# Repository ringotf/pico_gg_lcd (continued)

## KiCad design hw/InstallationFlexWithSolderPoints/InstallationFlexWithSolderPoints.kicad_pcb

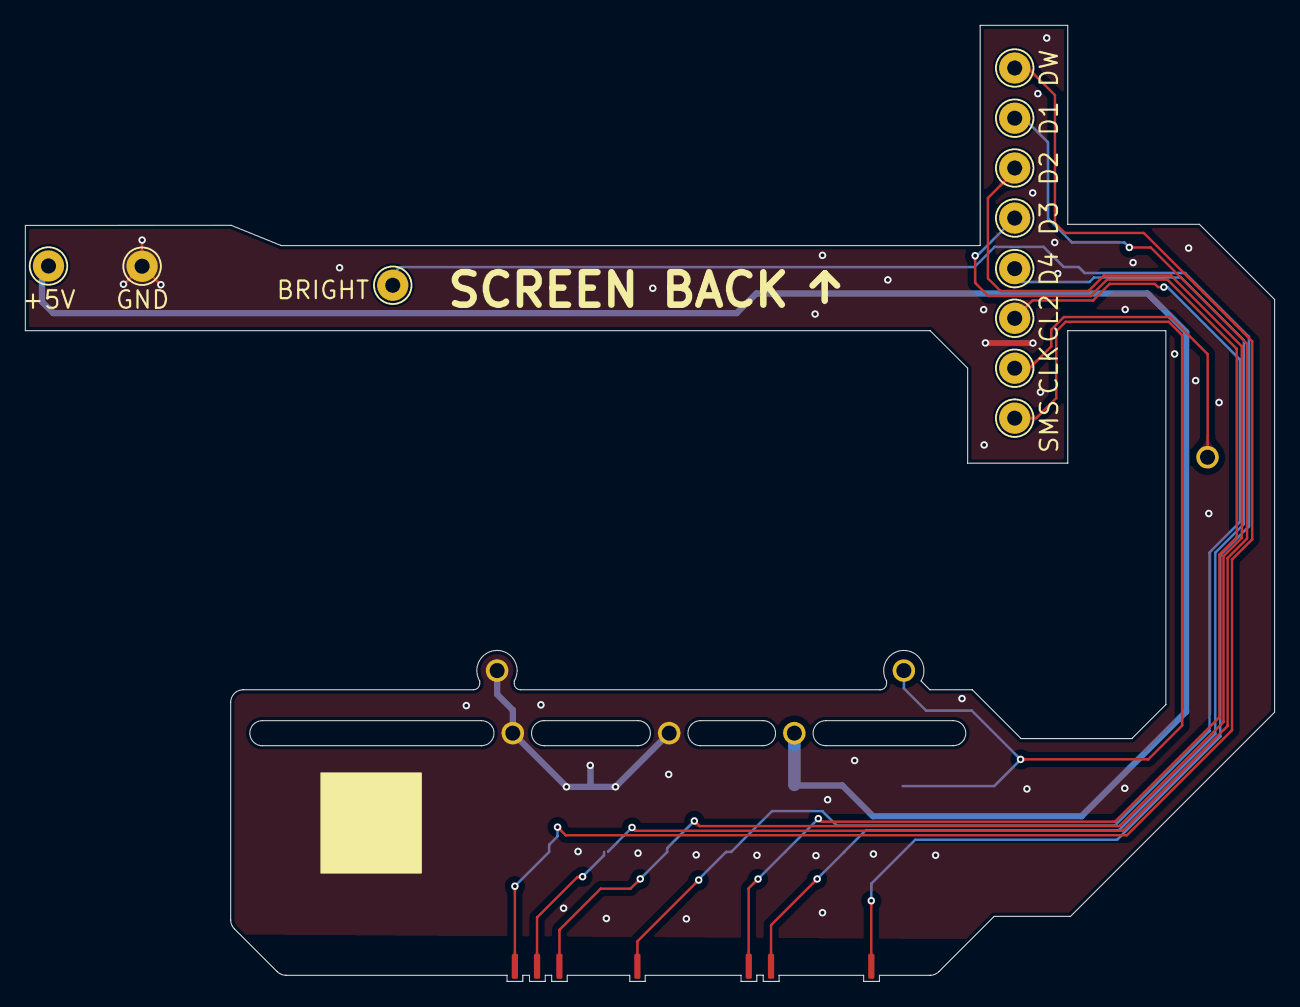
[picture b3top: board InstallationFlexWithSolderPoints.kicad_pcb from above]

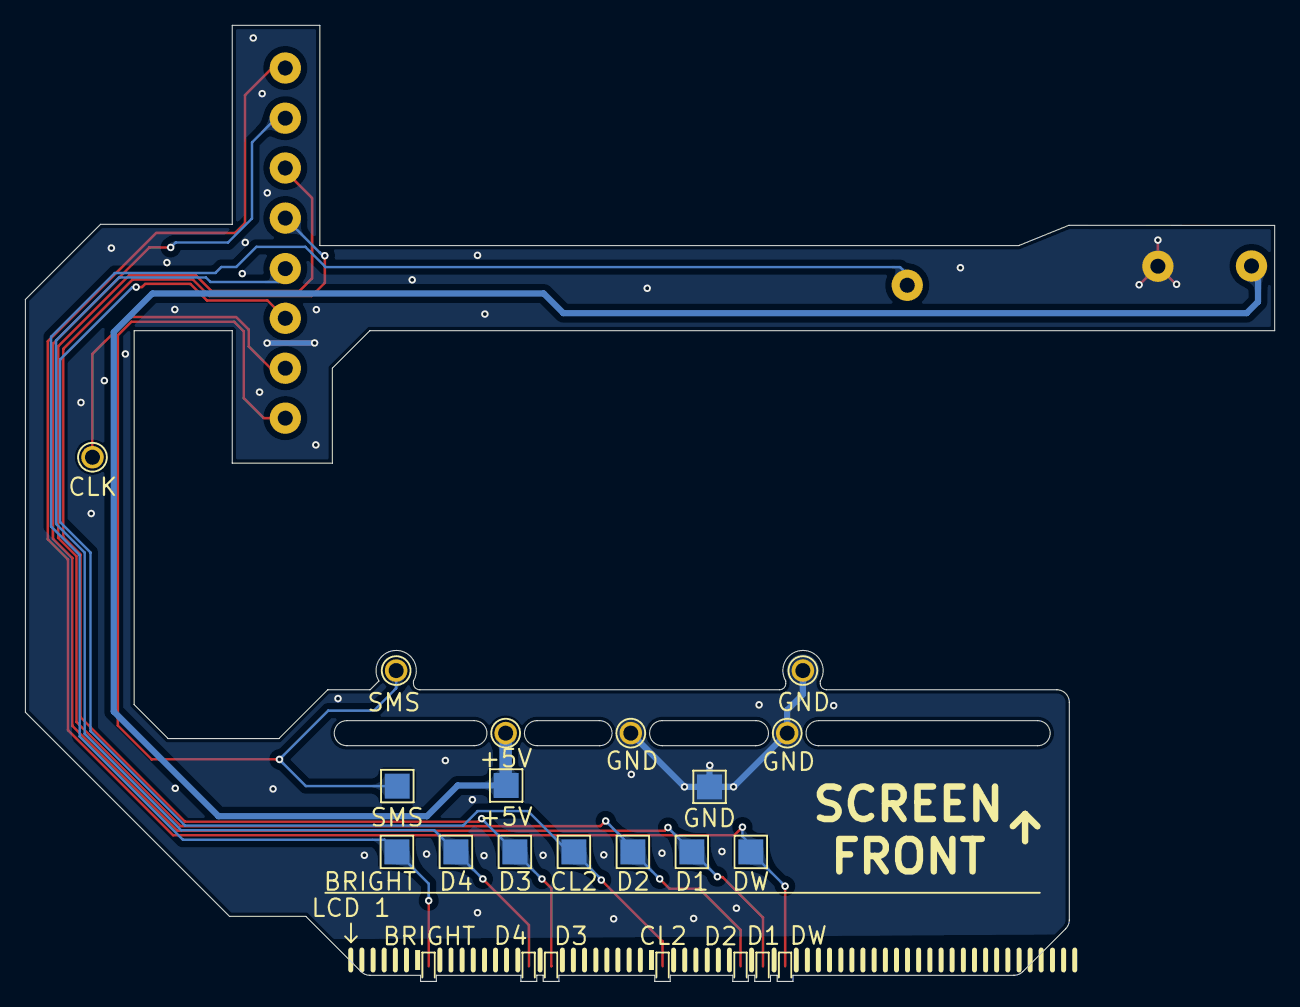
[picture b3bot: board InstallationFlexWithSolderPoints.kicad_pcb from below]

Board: 2 copper layers, 99.8 x 76.4 mm, 34 parts (16 on the bottom side), 11 nets.

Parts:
J1: +5V; TestPoint_THTPad_D2.5mm_Drill1.2mm
J2, J15, J16: GND; TestPoint_THTPad_D2.5mm_Drill1.2mm
J3: CLK; TestPoint_THTPad_D2.5mm_Drill1.2mm
J4: SMS; TestPoint_THTPad_D2.5mm_Drill1.2mm
J5: DW; SolderWirePad_1x01_Edge_1x2mm
J6: CL2; SolderWirePad_1x01_Edge_1x2mm
J7: D1; SolderWirePad_1x01_Edge_1x2mm
J8: D2; SolderWirePad_1x01_Edge_1x2mm
J9: D3; SolderWirePad_1x01_Edge_1x2mm
J10: D4; SolderWirePad_1x01_Edge_1x2mm
J11: BRIGHT; SolderWirePad_1x01_Edge_1x2mm
J18: GND; TestPoint_THTPad_D2.5mm_Drill1.2mm_Front
J20: +5V; TestPoint_THTPad_D2.5mm_Drill1.2mm_Front
J21: SMS; TestPoint_THTPad_D2.5mm_Drill1.2mm_Front
J22: CLK; TestPoint_THTPad_D2.5mm_Drill1.2mm_Front
J23: CL2; TestPoint_THTPad_D2.5mm_Drill1.2mm_Front
J24: D4; TestPoint_THTPad_D2.5mm_Drill1.2mm_Front
J25: D3; TestPoint_THTPad_D2.5mm_Drill1.2mm_Front
J26: D2; TestPoint_THTPad_D2.5mm_Drill1.2mm_Front
J27: D1; TestPoint_THTPad_D2.5mm_Drill1.2mm_Front
J28: DW; TestPoint_THTPad_D2.5mm_Drill1.2mm_Front
J29: BRIGHT; TestPoint_THTPad_D2.5mm_Drill1.2mm_Front
TP1: +5V; TestPoint_Pad_2.0x2.0mm
TP2: GND; TestPoint_Pad_2.0x2.0mm
TP4: SMS; TestPoint_Pad_2.0x2.0mm
TP5: DW; TestPoint_Pad_2.0x2.0mm
TP6: CL2; TestPoint_Pad_2.0x2.0mm
TP7: D4; TestPoint_Pad_2.0x2.0mm
TP8: D3; TestPoint_Pad_2.0x2.0mm
TP9: D2; TestPoint_Pad_2.0x2.0mm
TP10: D1; TestPoint_Pad_2.0x2.0mm
TP11: BRIGHT; TestPoint_Pad_2.0x2.0mm

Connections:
+5V: J1.1, J20.1, TP1.1
BRIGHT: J11.1, J29.1, TP11.1
CL2: J6.1, J23.1, TP6.1
CLK: J3.1, J22.1
D1: J7.1, J27.1, TP10.1
D2: J8.1, J26.1, TP9.1
D3: J9.1, J25.1, TP8.1
D4: J10.1, J24.1, TP7.1
DW: J5.1, J28.1, TP5.1
GND: J2.1, J15.1, J16.1, J18.1, TP2.1
SMS: J4.1, J21.1, TP4.1

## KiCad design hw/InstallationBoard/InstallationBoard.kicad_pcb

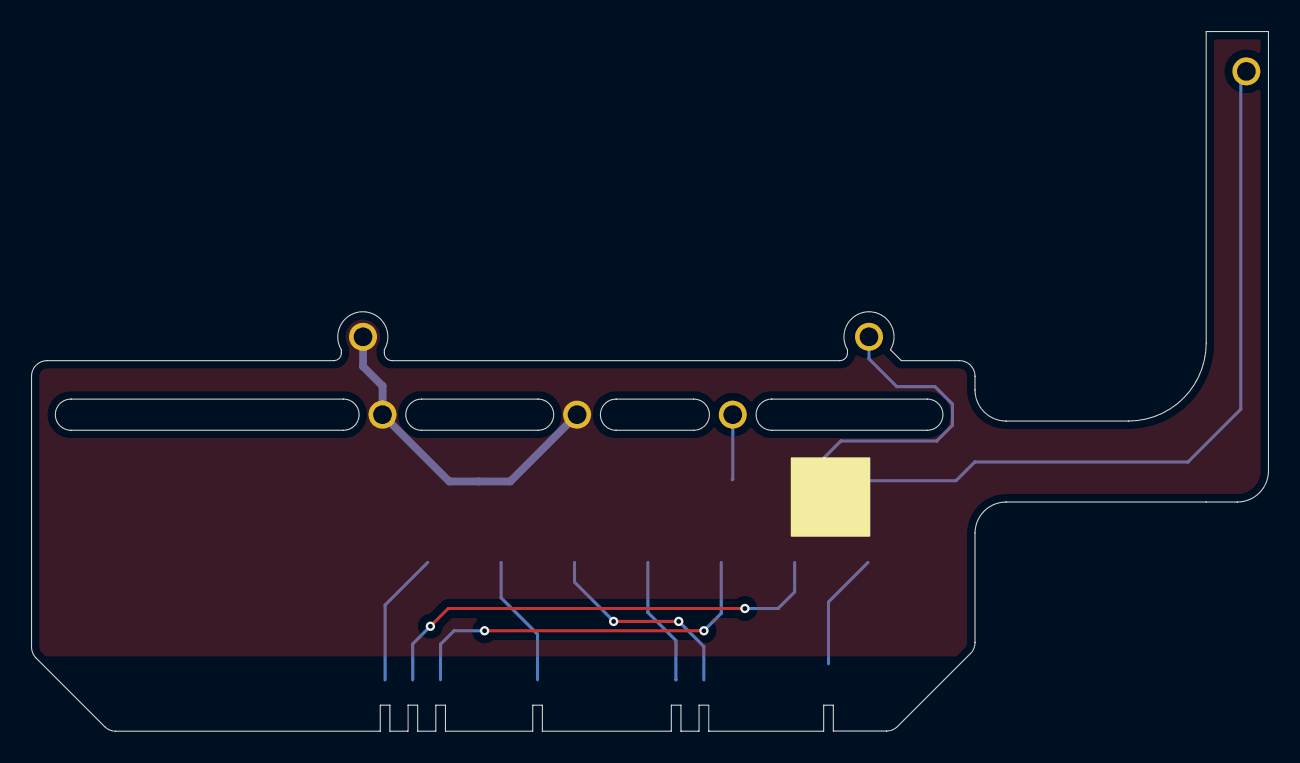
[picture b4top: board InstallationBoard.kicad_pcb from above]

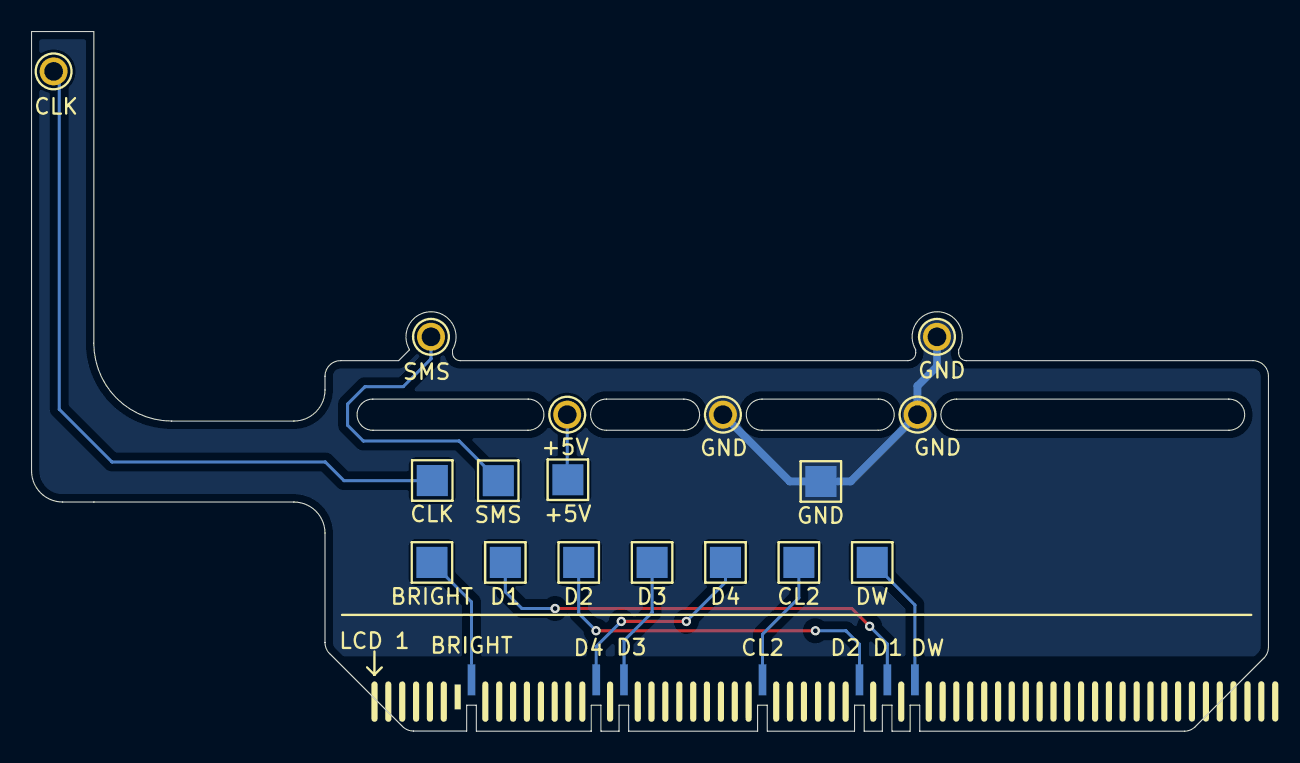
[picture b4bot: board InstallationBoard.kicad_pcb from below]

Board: 2 copper layers, 79.5 x 44.9 mm, 24 parts (24 on the bottom side), 11 nets.

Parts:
J1: +5V; TestPoint_THTPad_D2.5mm_Drill1.2mm
J2, J15, J16: GND; TestPoint_THTPad_D2.5mm_Drill1.2mm
J3: CLK; TestPoint_THTPad_D2.5mm_Drill1.2mm
J4: SMS; TestPoint_THTPad_D2.5mm_Drill1.2mm
J5: DW; SolderWirePad_1x01_SMD_1x2mm
J6: CL2; SolderWirePad_1x01_SMD_1x2mm
J7: D1; SolderWirePad_1x01_SMD_1x2mm
J8: D2; SolderWirePad_1x01_SMD_1x2mm
J9: D3; SolderWirePad_1x01_SMD_1x2mm
J10: D4; SolderWirePad_1x01_SMD_1x2mm
J11: BRIGHT; SolderWirePad_1x01_SMD_1x2mm
TP1: +5V; TestPoint_Pad_2.0x2.0mm
TP2: GND; TestPoint_Pad_2.0x2.0mm
TP3: CLK; TestPoint_Pad_2.0x2.0mm
TP4: SMS; TestPoint_Pad_2.0x2.0mm
TP5: DW; TestPoint_Pad_2.0x2.0mm
TP6: CL2; TestPoint_Pad_2.0x2.0mm
TP7: D1; TestPoint_Pad_2.0x2.0mm
TP8: D2; TestPoint_Pad_2.0x2.0mm
TP9: D3; TestPoint_Pad_2.0x2.0mm
TP10: D4; TestPoint_Pad_2.0x2.0mm
TP11: BRIGHT; TestPoint_Pad_2.0x2.0mm

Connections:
+5V: J1.1, TP1.1
BRIGHT: J11.1, TP11.1
CL2: J6.1, TP6.1
CLK: J3.1, TP3.1
D1: J7.1, TP7.1
D2: J8.1, TP8.1
D3: J9.1, TP9.1
D4: J10.1, TP10.1
DW: J5.1, TP5.1
GND: J2.1, J15.1, J16.1, TP2.1
SMS: J4.1, TP4.1

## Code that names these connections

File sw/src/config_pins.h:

//pin config in separate file for when differnt pin configs end up being needed for different pcb versions...

#pragma once

//libdvi output
#define dvi_d2_pins_base 0
#define dvi_d1_pins_base 2
#define dvi_d0_pins_base 4
#define dvi_clk_pins_base 6

//direct to lcd control
#define lcd_den 8
#define lcd_clk 9
#define lcd_rst 10

//gg video capture
#define gg_D1_pin 11 
#define gg_D2_pin 12 
#define gg_D3_pin 13 
#define gg_D4_pin 14 

#define gg_cl2_pin 15   //hsync
#define gg_dw_pin 16    //vsync
//#define gg_clk_pin 17   //sub-pixel RGB clock - not needed in current build, virtual clock is derived using PIO clock divider


//serial-to-parallel lcd shift registers
#define lcd_spi_latch 18
#define lcd_spi_clk 19
#define lcd_spi_mosi_1 23
#define lcd_spi_mosi_2 24
#define lcd_spi_mosi_3 25

//parallel-to-serial "SMS/GG" and button inputs shift register
#define btn_sr_miso 20
#define btn_sr_load 21
#define btn_sr_clk 22

//adc audio capture
#define gg_audio_r_pin 26
#define gg_audio_l_pin 27

//adc brightness controls
#define brightness_pot 28
#define lcd_dim 29

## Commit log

2025-10-14 imported to vscode
2025-10-25 Updated ignored files
2025-10-25 Added 54PinToRibbonAdapterBoard KiCad project
2025-10-30 Updated FPC connector on 54 Pin Adapter Board
2025-10-30 Updated PCB:
    - Changed Pico pin assignment, so differential pairs can be tuned and Game Gear connections optimised if needed (code needs refreshing to match)
    - Changed PWM components to SMD versions, and moved to left side of board away from the Game Gear's oscillator
    - Moved 5V and GND connection points to left side with PWM components
    - Repositioned holes for the the FPC adapter board to align the connector for the LCD position
    - Added footprint for an FPC connector as alternative to an adapter board
    - HDMI differential pairs tuned to about 44.444mm length
2025-10-30 Added WIP InstallationBoard kicad project
2025-10-30 Added WIP InstallationFlex PCB
2025-10-30 Added "gg_" prefix to game gear pin constant
    Updated pin assignments to match PCB
    Added usb streaming of framebuffer and a python script to view for testing purposes
    WIP - trying to fix lines missing from start of frame
    WIP - tweaking the PWM frequency
2025-11-09 Corrected pin assignments to be sequential.
    Added some pwm variables.
    Added pwm feedback logic to run on core1.
    Commented out brightness control for now, probably needs combining with the pwm feedback logic to regulate the pwm voltage target.
    Temporarily forced the GG output and disabled the SMS output.
2025-11-09 Updated pin assignments on main PCB to match pico code using the correct sequential pins.
    54PinTo60RibbonAdapterBoard tweaked trace layout to reduce overall board size slightly.
    Added InstallationFlexWithSolderPoints for installing without a ribbon connector.
2025-11-09 Added initial version of frame stl file
2025-11-09 Update pin assignments in gg_capture.pio
    Added a wait_cycles to lcd_send.pio as it seemed a little quick
2025-11-11 Added wip LCDRibbonDevTest
2025-11-11 Corrected resistor values and part numbers.
    Tweaked board outline to avoid resistor on GG.
    Rerouted +3V3 around board.
2025-11-11 Fixed second frame buffer overlapping with the first.
2025-11-14 index on vscode-import: 2af1a2f Corrected resistor values and part numbers.
2025-11-14 Tweaked pio programs so waits are done with square bracket notation
2025-11-14 Increased text size on installation flex
2025-11-15 Started wip for a higher-res screen. Should be outputting a signal up to 1280x720, which seems to be what the 640x480 screens need to be driven by in parallel rgb.
    This uses the first 12 gpio pins for the B4G4R4 output, so all the pins have been reassigned for now.
2025-11-16 Updated 54/60 Pin FPC connector footprint.
2025-11-21 Wip updates for HDMI support.
2025-11-27 Updated PicoDVI (libdvi) with audio support from ikjordan fork.
    Started adding code to process GG audio but need to reorder pins to free up ADC pins, or use a separate ADC module. Still very WIP.
    The audio-less HDMI works, but needs temporary work around to reverse bit order as the pins on the pcb are wrong way around.
    Added main.h to start adding any shared constant defines.
    Added constants to specify the pio instance and state machine to use for each program.
    Added a front horizontal porch pio program "front_h_porch" to avoid capturing some pixels.
2025-11-27 Started updating PCB to support being rotated 180 degrees to allow LCD ribbon to be fed underneath instead of over the top.
    Switched pins of brightness/pwm feedback so they dont cross over each other.
2025-11-29 Wip 4x and 2x lcd_send working with parallel rgb on 320x240 screens...
2025-11-30 640x480 screen tentatively "working"
2025-12-03 Added lcd_send_spi to serialise the frame data to 2 shift registers which connect to the lcd, allows 60fps 640x480 12bit RGB444.
    Pins assignments to be corrected.
2025-12-03 Tweaked board outline.
2025-12-05 Higher res screen works well with 3 shift registers for 70-80fps, so overhead for other processing between frames, but requires a pin for each shift register serial in so 3 MOSI pins.
    This is with 4x horizontal and 3x vertical scaling for GG, with header and footer lines.
    2 shift registers works ok at about 60fps but seems to be pushing the registers response times.
    Disabled the DMA channels that discard lines, think at least 1 line was actual frame that was getting lost.
2025-12-05 Updated code with pio constants following previous merge.
    Fixed capture without the DMA channel skipping lines.
2025-12-10 HDMI with audio working, but audio quality depends on audio source, but under 60fps as lcd_send_spi is now a single program on a single state machine but can be faster when run across 2.
    Pin assignments all unconfirmed for now.
2025-12-11 Started updating PCB and schematic, adding shift registers, audio lines, and changing to separate pwm module to save pins.
2025-12-14 Updated pins to match current prototype.
    Added SPI for an input shift register for buttons.
    Started adding a basic overlay.
2025-12-16 Restored framebuffer swapping for video outputs.
    Centered hdmi output, with 4x horizontal and 3x vertical scaling which matches the lcd output.
    Added title, fps counter, and button status to overlay, although it flickers on hdmi out as overlay is only drawn during the lcd output.
2025-12-16 Updated PIO capture and send programs so they can all run on a single PIO core.
    - vblank instructions moved to hblank, so vblank program not needed
    - lcd_send_spi and lcd_send_clk moved to pio0 to improve lcd update performance
2025-12-17 Mostly updated kicad project to match current prototype
    - Pick-And-Place SMT components moved to PCB backside
    - Hand solder components, i.e. ribbon connectors , stay on front side
    - Ribbon connectors for GG data and control inputs
    - Ribbon connector for "DVI" output connector
    - Shift registers for LCD
    - 3.3v buck circuit instead of using Pico circuit to help minimise ADC noise
2025-12-19 More PCB tweaks, added some bypass caps, changed some pin assignments to improve board layout
2025-12-19 Added TestPoints to updated PCB for manual soldering install without a ribbon.
2025-12-22 Added NewInstallationRibbon that unfolds across the motherboard with 2 ribbon connections on each side and solder points for all the game gear inputs and video data.
    Updated some pin assignments to help with layout of the installation ribbon, to reduce signals crossing over each other.
2025-12-23 Added LM358 op-amp for both audio channels.
    Updated ribbon connector pin assignments, text labels, and tweaked board outline.
    Gerbers updated for production.
2025-12-25 Corrected some component positions
    Updated lcd frame design
2026-01-11 PCB fixes for second prototype boards:
    Fixed DIR pin on transceiver/level shifter not being tied high.
    Fixed /SRCLR pin on shift registers not being tied high.
    Tied Pico VBUS to +5V so usb can power the board.
    Increased hole size on mounting points.
2026-01-25 Main PCB updated for third prototype boards. Most things moved around and rerouted. Also:
    - Audio circuit changed to use LMV321 op amp, with zero-ohm resistors as placeholders for tweaks.
    - Flex PCB Input connector changed to a single 24pin connection.
    - Video out changed to normal type-a instead of micro, and moved across board.
    - Shift registers changed to 5v with voltage dividers on data lines to lcd.
    - Diode footprints changed to smaller SOD-323.
    - Added diode and trace from Pico VBUS to +5v so the board will run from USB.
2026-01-25 Flex PCB updated:
    - Use a single 24pin connection to the main board, pin out updated to match the main board.
    - Various layout tweaks to improve installation by reducing some of the slack.
    - Added rule areas around solder points to exclude copper fills to help align the solder points.
    - Added guide holes for the top row of cartridge connector pins, and tweaked the other guide holes to help with install.
2026-01-25 Added 3d prints for the two different style micro video out connector boards.
2026-01-28 Fixed hdmi lines having capacitors instead of resistors.
2026-02-08 Fixed voltage divider in audio ADC circuit.
2026-02-11 WIP commit of working audio capture, uses last 2 DMA channels, chained together for the audio ring buffer. Sounds good, could be amplified more.
2026-02-13 Fixed wrong GND pin on installation ribbon!
2026-02-26 Rearranged shift register RGB sequence to fix needing to left-shift the pixel data 20 bits.
    Moved "Video Out" connector for better clearance in the case.
    Changed some individual resistors for resistor arrays.
2026-02-26 PCB updated for 4th prototype.
    Tweaked board outline, added 3rd screw hole back.
2026-03-09 WIP tweaks for fixing the bit shifting required for the serial to parallel shift registers.
2026-03-16 Updated hdmi pin assignments to match pcb.
    Removed bit shifting for the lcd shift registers as the pcb is now corrected.
    Tweaked frame capture to include some lines after vblank so the very first real line can be caught.
    Started removing waits for the gg pixel clock pin and use delay cycles instead as the timing is currently about 7 delays cycles per pixel when overlocked to 252mhz for libdvi.
2026-03-17 Updated get_data pio program to use a clock divider to match the gg pixel clock, so it doesn't need a clock pin anymore and is synced to the hsync signal with the same 32.2mhz timing as the gg... ass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
    Started tidying code up, and trying to fix other vsync issues with both lcd and libdvi.
2026-03-26 Tidied code and repository.
    Added header file for pin assignments.
    Added cmake options to .gitignore and removed cmakefiles folder
    Deleted old installation ribbon projects.
    Moved 3dprint files.
    Generated schema.
2026-03-26 WIP started removing the GG clock signal and enabling Hot Plug Detect.
    Started updating the lcd dimming circuit.
2026-04-06 Updated video capture and output to support SMS
2026-04-06 Added 2x horizontal scaling for lcd
2026-04-08 Switching between GG and SMS mode now works
2026-04-09 Updated readme with details of WL355608 prototype
2026-04-09 Added some relevant datasheets to docs
